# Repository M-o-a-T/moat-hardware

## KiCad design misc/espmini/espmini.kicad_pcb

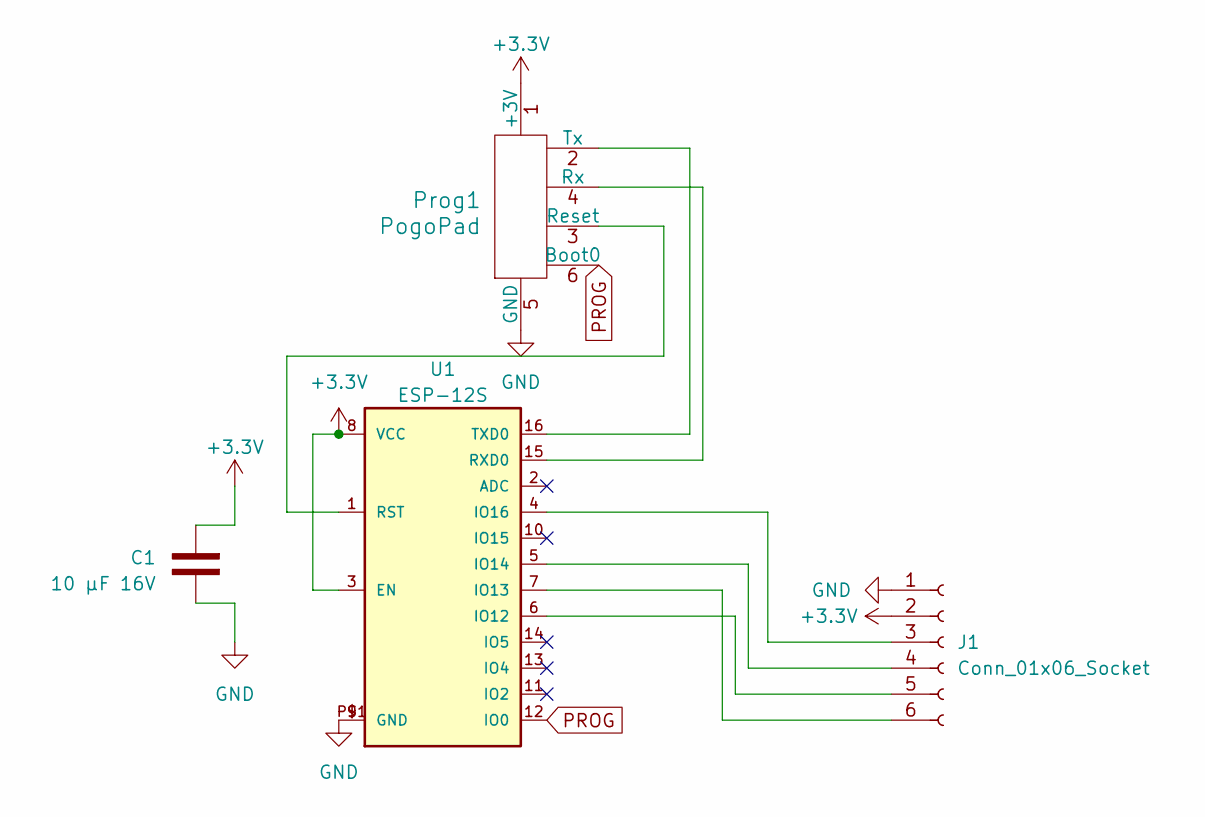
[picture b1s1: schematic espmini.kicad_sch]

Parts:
C1: CP_10µ_16V_0603; C_0805_2012Metric_Pad1.18x1.45mm_HandSolder
J1: Conn_01x06_Socket; Pads_1x06_P2.00mm
Prog1: PogoPad; 2X3_PAD
U1: ESP-12S

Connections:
+3V3: C1.1, J1.2, Prog1.1 (+3V), U1.3 (EN), U1.8 (VCC)
GND: C1.2, J1.1, Prog1.5 (GND), U1.9 (GND), U1.P$1 (GND)
unnamed: J1.3, U1.4 (IO16)
unnamed: J1.4, U1.5 (IO14)
unnamed: J1.5, U1.6 (IO12)
unnamed: J1.6, U1.7 (IO13)
unnamed: Prog1.3 (Reset), U1.1 (RST)
unnamed: Prog1.4 (Rx), U1.15 (RXD0)
unnamed: Prog1.2 (Tx), U1.16 (TXD0)
PROG: Prog1.6 (Boot0), U1.12 (IO0)

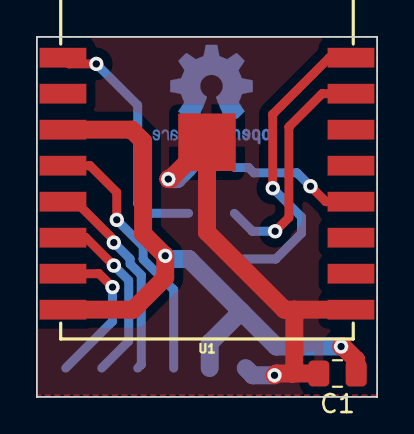
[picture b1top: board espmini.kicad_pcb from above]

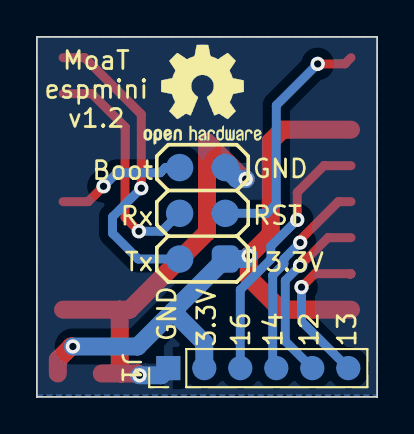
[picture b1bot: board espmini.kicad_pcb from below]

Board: 2 copper layers, 18.9 x 20.0 mm, 4 parts (2 on the bottom side), 10 nets.

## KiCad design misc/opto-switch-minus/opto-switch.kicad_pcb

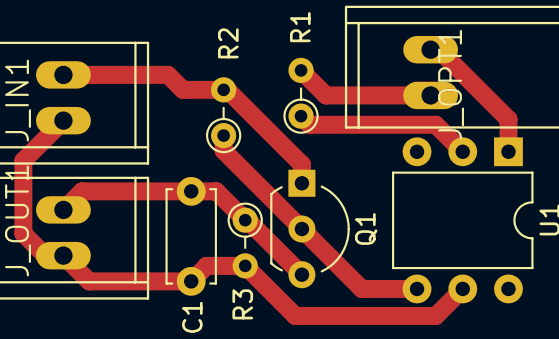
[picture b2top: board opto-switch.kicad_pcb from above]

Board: 2 copper layers, 9 parts (0 on the bottom side), 7 nets.

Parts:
C1: C; C_Disc_D5.0mm_W2.5mm_P5.00mm
J_IN1: Conn_01x02; 1X02_GN
J_OPT1: Conn_01x02; 1X02_GN
J_OUT1: Conn_01x02; 1X02_GN
Q1: 2N7002; TO-92L_Inline_Wide
R1: R_180_0603; R_Axial_DIN0204_L3.6mm_D1.6mm_P2.54mm_Vertical
R2: R 100k; R_Axial_DIN0204_L3.6mm_D1.6mm_P2.54mm_Vertical
R3: R 10k; R_Axial_DIN0204_L3.6mm_D1.6mm_P2.54mm_Vertical
U1: MOC8101; DIP-6_W7.62mm

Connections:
GND: J_IN1.2, Q1.1 (S), R2.2
unnamed: C1.1, J_IN1.1, J_OUT1.1, R3.2, U1.5
unnamed: J_OPT1.1, U1.1
unnamed: J_OPT1.2, R1.2
unnamed: C1.2, J_OUT1.2, Q1.3 (D), R3.1
unnamed: Q1.2 (G), R2.1, U1.4
unnamed: R1.1, U1.2

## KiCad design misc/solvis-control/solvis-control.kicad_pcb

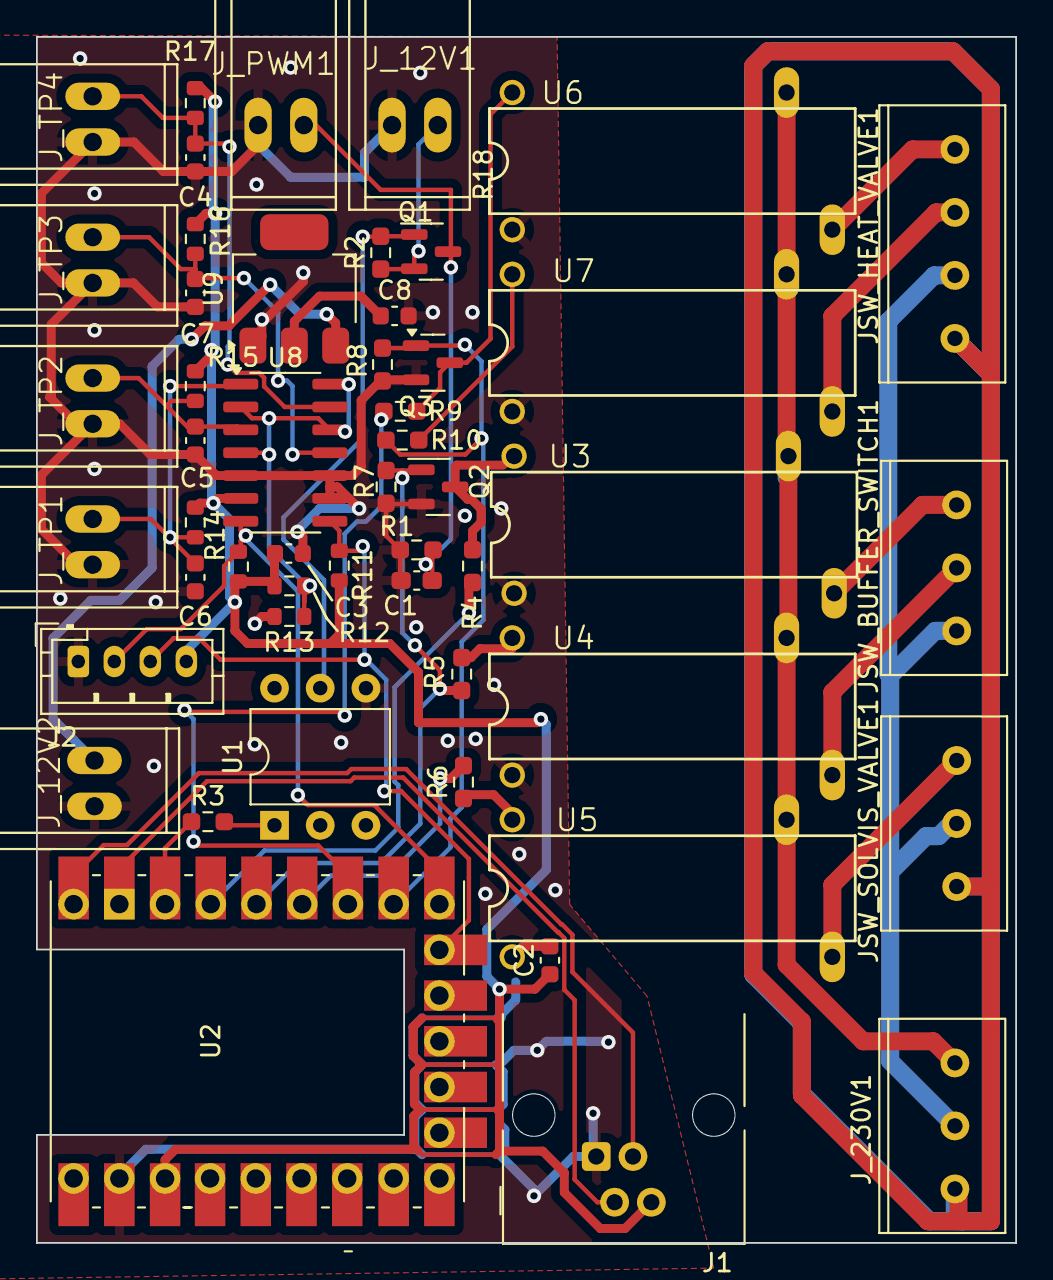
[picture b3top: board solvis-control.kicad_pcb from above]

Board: 2 copper layers, 54.4 x 67.0 mm, 51 parts (0 on the bottom side), 36 nets.

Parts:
C1: C; C_0603_1608Metric_Pad1.08x0.95mm_HandSolder
C2: CP_10µ_16V_0603; C_0603_1608Metric
C3: CP_1µ_0603; C_0603_1608Metric
C4, C5, C6, C7: CP_100n_50V_0603; C_0603_1608Metric
C8: C_1µ_25V_0603; C_0603_1608Metric
J1: Conn_01x04_Socket; RJ11
J2: Conn_01x04_Socket; JST_PH_B4B-PH-K_1x04_P2.00mm_Vertical
JSW_BUFFER_SWITCH1: Conn_01x03_Socket; Würth3.5mm_3
JSW_HEAT_VALVE1: Conn_01x04_Socket; Würth3.5mm_4
JSW_SOLVIS_VALVE1: Conn_01x03_Socket; Würth3.5mm_3
J_12V1, J_12V2: Conn_01x02; 1X02_GN
J_230V1: Conn_01x03_Socket; Würth3.5mm_3
J_PWM1: Conn_01x02; 1X02_GN
J_TP1, J_TP2, J_TP3, J_TP4: Conn_01x02; 1X02_GN
Q1: SI2390DS; SOT-23
Q2, Q3: 2N7002; SOT-23
R1: R 10k; R_0603_1608Metric_Pad0.98x0.95mm_HandSolder
R2, R7, R8: R 100k; R_0603_1608Metric_Pad0.98x0.95mm_HandSolder
R3: R_180_0603; R_0603_1608Metric_Pad0.98x0.95mm_HandSolder
R4, R5, R6, R9, R10: R_360_0603; R_0603_1608Metric_Pad0.98x0.95mm_HandSolder
R11, R12, R13, R14, R15, R16, R17, R18: R_1k_0603; R_0603_1608Metric
U1: MOC8101; DIP-6_W7.62mm
U2: RPi_Ali_SMD_TH
U3, U4, U5, U6, U7: CPC1965G; DIL16-CPC1965G
U8: MCP3428x-xSL; SOIC-14_3.9x8.7mm_P1.27mm
U9: AZ1117-3.3; SOT-223

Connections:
+3.3V: C2.1, C3.1, J1.4, J2.4, R11.2, R12.1, R14.2, R15.1, R16.2, R17.1, R18.2, U2.21 (3V3), U8.6 (V_{DD})
+3V3: C8.1, U9.2 (VO)
+12V: J_12V2.2, U9.3 (VI)
/ADCREF: R12.2, R13.1, U8.2 (CH1-), U8.4 (CH2-), U8.12 (CH3-), U8.14 (CH4-)
/L: J_230V1.1, U3.10 (A1), U4.10 (A1), U5.10 (A1), U6.10 (A1), U7.10 (A1)
/N: JSW_BUFFER_SWITCH1.3, JSW_HEAT_VALVE1.3, JSW_SOLVIS_VALVE1.2, J_230V1.2
/PE: JSW_HEAT_VALVE1.4, JSW_SOLVIS_VALVE1.3, J_230V1.3
/SCL: J2.3, R11.1, U2.10 (GPIO9), U8.8 (SCL)
/SDA: J2.2, R18.1, U2.9 (GPIO8), U8.7 (SDA)
GND: C1.2, C2.2, C3.2, C4.2, C5.2, C6.2, C7.2, C8.2, J1.1, J2.1, J_12V1.1, J_12V2.1, J_PWM1.1, J_TP1.1, J_TP2.1, J_TP3.1, J_TP4.1, Q2.2 (S), Q3.2 (S), R1.2, R7.2, R8.2, R13.2, U1.2, U1.4, U2.22 (GND), U3.1 (-), U4.1 (-), U5.1 (-), U6.1 (-), U7.1 (-), U8.5 (V_{SS}), U8.9 (Adr0), U8.10 (Adr1), U9.1 (ADJ)
unnamed: J1.2, U2.2 (GPIO1)
unnamed: J1.3, U2.1 (GPIO0)
unnamed: JSW_BUFFER_SWITCH1.1, U3.8 (A2)
unnamed: JSW_BUFFER_SWITCH1.2, U4.8 (A2)
unnamed: JSW_HEAT_VALVE1.1, U6.8 (A2)
unnamed: JSW_HEAT_VALVE1.2, U7.8 (A2)
unnamed: JSW_SOLVIS_VALVE1.1, U5.8 (A2)
unnamed: J_12V1.2, Q1.2 (S), R2.1
unnamed: C1.1, J_PWM1.2, Q1.3 (D), R1.1
unnamed: C6.1, J_TP1.2, R14.1, U8.1 (CH1+)
unnamed: C5.1, J_TP2.2, R15.2, U8.3 (CH2+)
unnamed: C7.1, J_TP3.2, R16.1, U8.11 (CH3+)
unnamed: C4.1, J_TP4.2, R17.2, U8.13 (CH4+)
unnamed: Q1.1 (G), R2.2, U1.5
unnamed: Q2.3 (D), R4.1, U3.16 (+)
unnamed: Q2.1 (G), R5.2, R7.1, U2.5 (GPIO4)
unnamed: Q3.3 (D), R9.1, U6.16 (+)
unnamed: Q3.1 (G), R8.1, R10.2, U2.8 (GPIO7)
unnamed: R3.2, U1.1
unnamed: R3.1, U2.3 (GPIO2)
unnamed: R4.2, U2.4 (GPIO3)
unnamed: R6.2, U2.6 (GPIO5)
unnamed: R9.2, U2.7 (GPIO6)
unnamed: R5.1, U4.16 (+)
unnamed: R6.1, U5.16 (+)
unnamed: R10.1, U7.16 (+)

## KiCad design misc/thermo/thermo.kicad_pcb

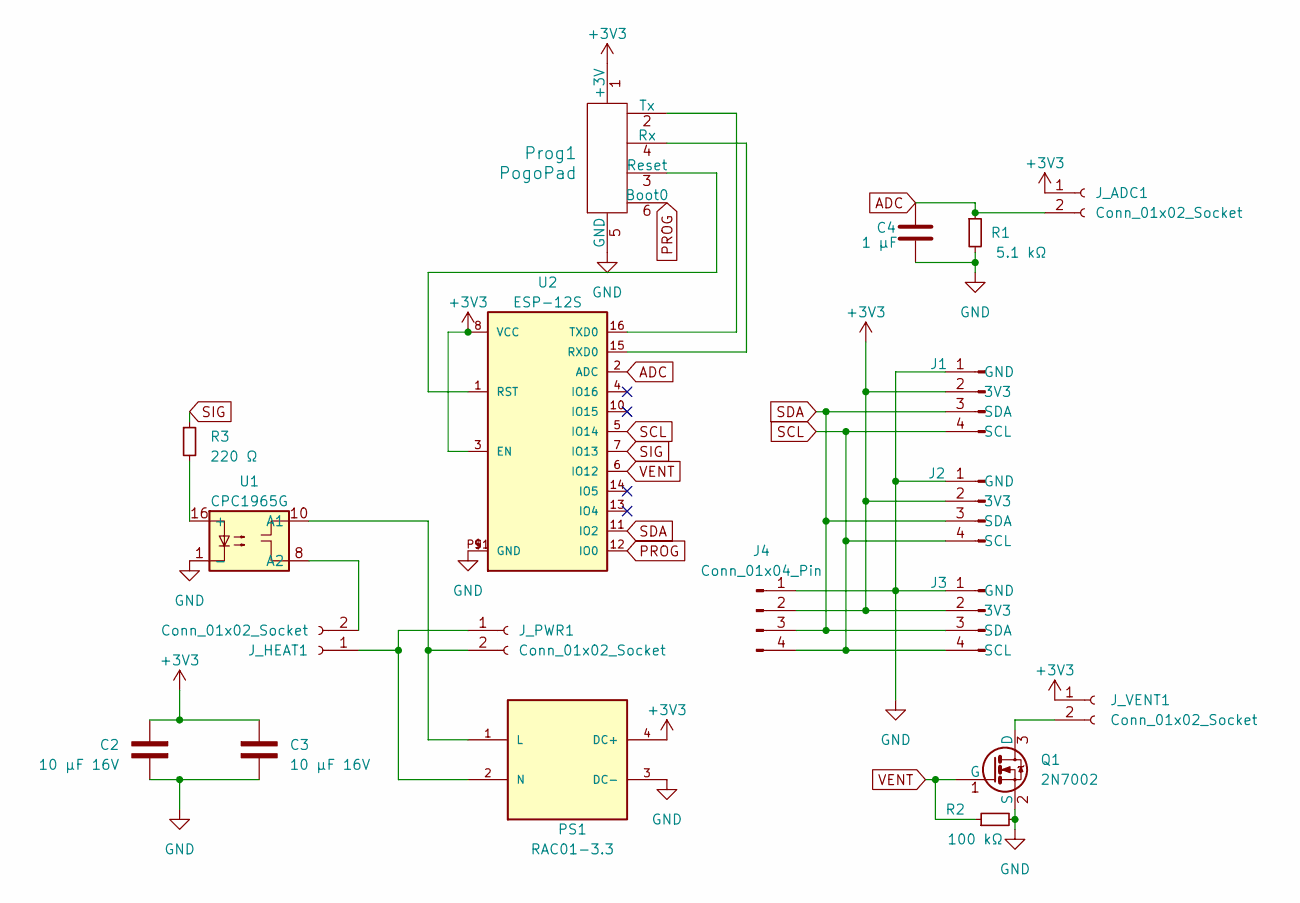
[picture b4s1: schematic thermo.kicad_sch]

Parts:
C2, C3: CP_10µ_16V_0603; C_0603_1608Metric
C4: CP_1µ_10V_0603; C_0603_1608Metric; Farnell 3013419
J1, J2, J3: Conn_01x04_Pin; JST_SH_BM04B-SRSS-TB_1x04-1MP_P1.00mm_Vertical
J4: Conn_01x04_Pin; PinHeader_1x04_P2.54mm_Vertical
J_ADC1: Conn_01x02_Socket; JST_XA_B02B-XASK-1_1x02_P2.50mm_Vertical
J_HEAT1: Conn_01x02_Socket; 1X02_GN
J_PWR1: Conn_01x02_Socket; 1X02_GN
J_VENT1: Conn_01x02_Socket; JST_XA_B02B-XASK-1_1x02_P2.50mm_Vertical
PS1: RAC01-3.3
Prog1: PogoPad; 2X3_PAD
Q1: 2N7002; SOT-23
R1: R_5k1_0603; R_0603_1608Metric; LCSC C23186
R2: R_100k_0603; R_0603_1608Metric
R3: R_220_0603; R_0603_1608Metric
U1: CPC1965G; DIL16-CPC1965G
U2: ESP-12S

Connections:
+3V3: C2.1, C3.1, J1.2 (3V3), J2.2 (3V3), J3.2 (3V3), J4.2, J_ADC1.1, J_VENT1.1, PS1.4 (DC+), Prog1.1 (+3V), U2.3 (EN), U2.8 (VCC)
ADC: C4.1, J_ADC1.2, R1.1, U2.2 (ADC)
GND: C2.2, C3.2, C4.2, J1.1 (GND), J2.1 (GND), J3.1 (GND), J4.1, PS1.3 (DC-), Prog1.5 (GND), Q1.2 (S), R1.2, R2.2, U1.1 (-), U2.9 (GND), U2.P$1 (GND)
unnamed: J_HEAT1.1, J_PWR1.1, PS1.2 (N)
unnamed: J_HEAT1.2, U1.8 (A2)
unnamed: J_PWR1.2, PS1.1 (L), U1.10 (A1)
unnamed: J_VENT1.2, Q1.3 (D)
unnamed: Prog1.3 (Reset), U2.1 (RST)
unnamed: Prog1.4 (Rx), U2.15 (RXD0)
unnamed: Prog1.2 (Tx), U2.16 (TXD0)
unnamed: R3.2, U1.16 (+)
PROG: Prog1.6 (Boot0), U2.12 (IO0)
SCL: J1.4 (SCL), J2.4 (SCL), J3.4 (SCL), J4.4, U2.5 (IO14)
SDA: J1.3 (SDA), J2.3 (SDA), J3.3 (SDA), J4.3, U2.11 (IO2)
SIG: R3.1, U2.7 (IO13)
VENT: Q1.1 (G), R2.1, U2.6 (IO12)

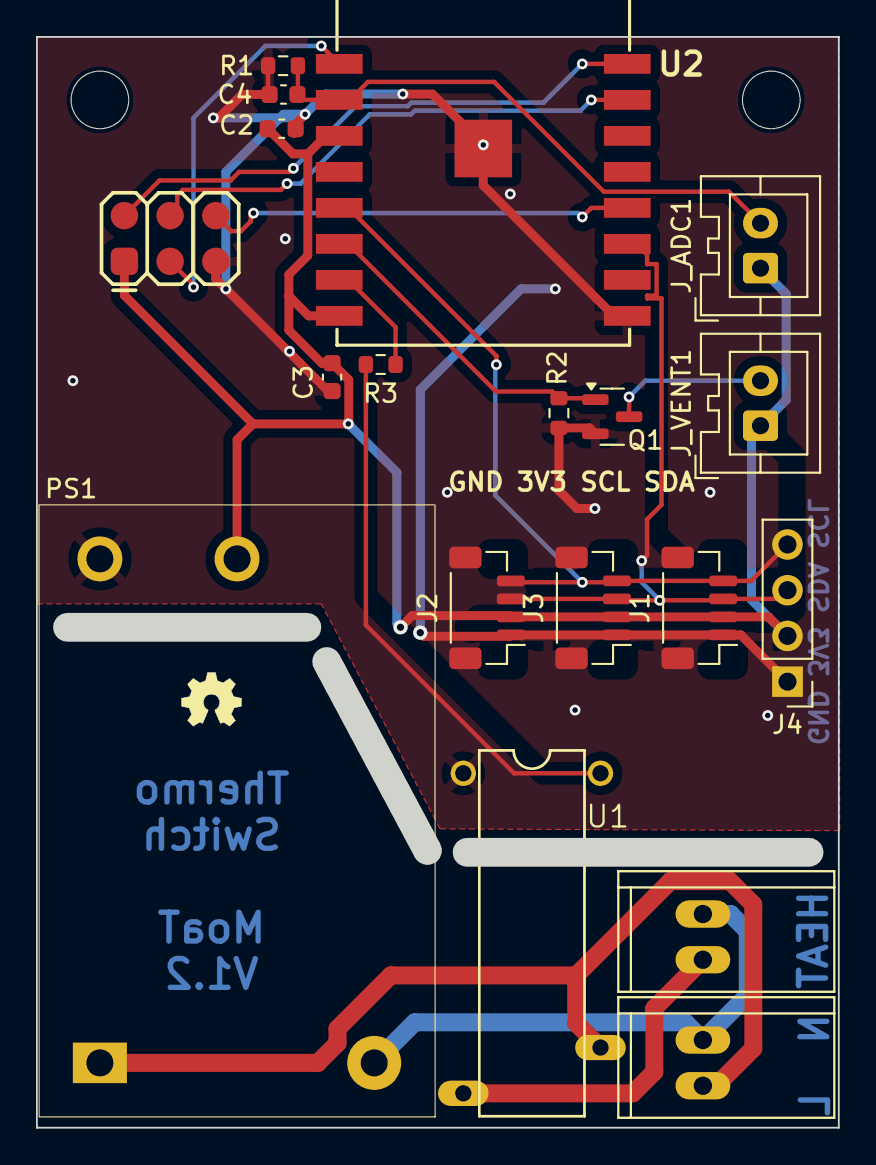
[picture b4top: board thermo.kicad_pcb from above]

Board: 2 copper layers, 44.5 x 60.6 mm, 19 parts (0 on the bottom side), 16 nets.

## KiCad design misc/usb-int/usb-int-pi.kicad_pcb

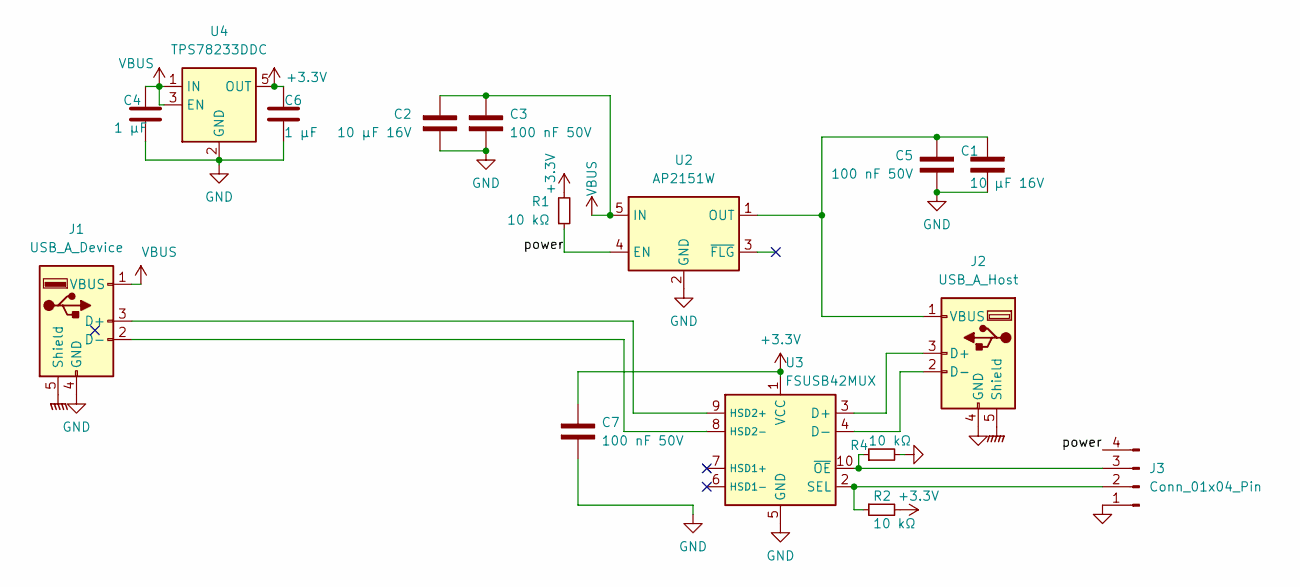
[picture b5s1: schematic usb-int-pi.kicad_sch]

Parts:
C1, C2: CP_10µ_16V_0603; C_0603_1608Metric
C3, C5, C7: CP_100n_16V_0603; C_0603_1608Metric; Farnell 3881081
C4, C6: CP_1µ_10V_0603; C_0603_1608Metric; Farnell 3013419
J1: USB_A_Device; SAMTEC_USB-AM-S-X-X-TH; Farnell 3551287
J2: USB_A_Host; USB_A_Stewart_SS-52100-001_Horizontal; Farnell 4126367
J3: Conn_01x04_Pin; PinHeader_1x04_P2.54mm_Horizontal
R1, R2, R4: R_10k_0603; R_0603_1608Metric; LCSC C25804
U2: AP2151W; SOT-23-5; Farnell 3482805
U3: FSUSB42MUX; MSOP-10_3x3mm_P0.5mm; Farnell 2564479
U4: TPS78233DDC; SOT-23-5

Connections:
+3V3: C6.1, C7.1, R1.2, R2.2, U3.1 (VCC), U4.5 (OUT)
/power: J3.4, R1.1, U2.4 (EN)
GND: C1.2, C2.2, C3.2, C4.2, C5.2, C6.2, C7.2, J1.4 (GND), J2.4 (GND), J3.1, R4.2, U2.2 (GND), U3.5 (GND), U4.2 (GND), U4.4 (GND)
GNDPWR: J1.5 (Shield), J2.5 (Shield)
unnamed: J1.3 (D+), U3.9 (HSD2+)
unnamed: J1.2 (D-), U3.8 (HSD2-)
unnamed: J2.3 (D+), U3.3 (D+)
unnamed: J2.2 (D-), U3.4 (D-)
unnamed: C1.1, C5.1, J2.1 (VBUS), U2.1 (OUT)
unnamed: J3.2, R2.1, U3.2 (SEL)
unnamed: J3.3, R4.1, U3.10 (~OE)
VBUS: C2.1, C3.1, C4.1, J1.1 (VBUS), U2.5 (IN), U4.1 (IN), U4.3 (EN)

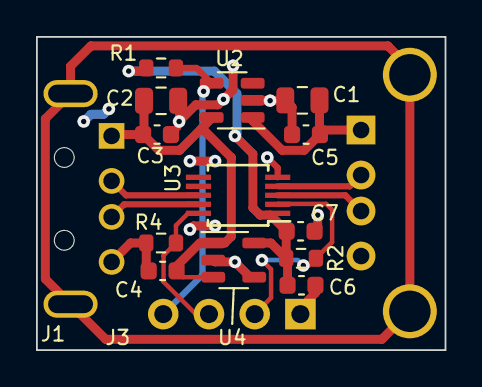
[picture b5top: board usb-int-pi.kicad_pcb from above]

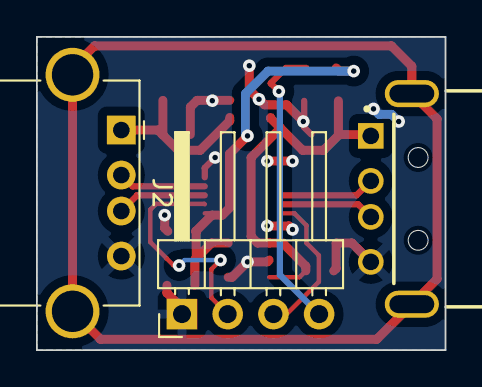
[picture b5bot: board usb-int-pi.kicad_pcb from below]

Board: 2 copper layers, 22.7 x 17.4 mm, 16 parts (3 on the bottom side), 12 nets.

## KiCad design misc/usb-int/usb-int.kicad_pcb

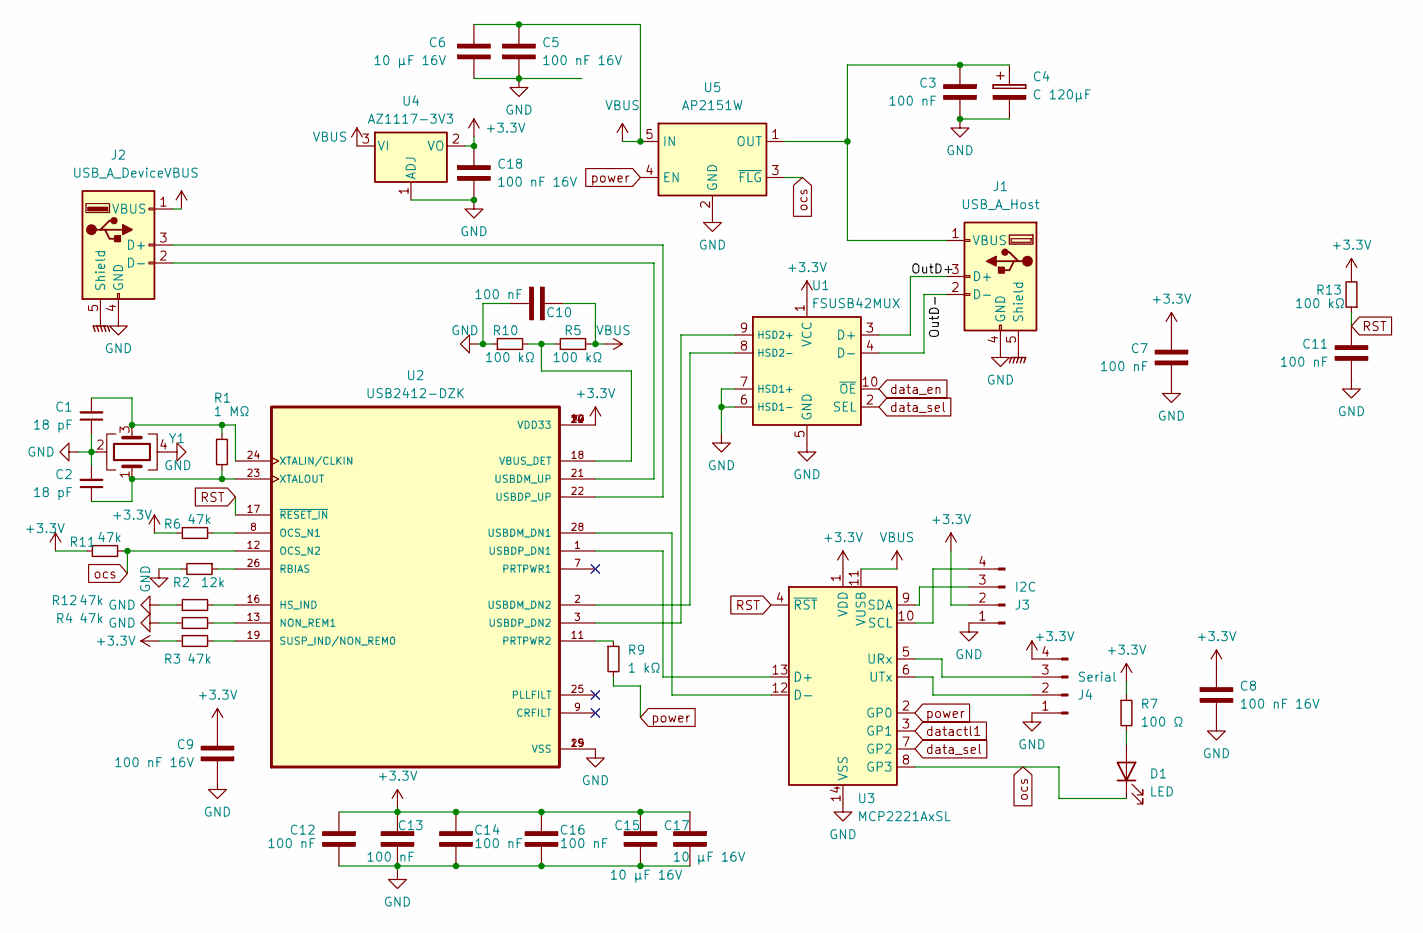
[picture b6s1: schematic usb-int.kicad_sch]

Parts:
C1, C2: 18 pF; C_0603_1608Metric; Farnell 1759056
C3, C5, C7, C8, C9, C10, C11, C12, C13, C14, C16, C18: CP_100n_16V_0603; C_0603_1608Metric; Farnell 3881081
C4: C 120µF; C_Elec_5x5.4; Farnell 2466648
C6, C15, C17: CP_10µ_16V_0603; C_0603_1608Metric
D1: LED; LED_0603_1608Metric
J1: USB_A_Host; USB_A_Stewart_SS-52100-001_Horizontal
J2: USB_A_Device; SAMTEC_USB-AM-S-X-X-TH; Farnell 3551287
J3: I2C; JST_SH_SM04B-SRSS-TB_1x04-1MP_P1.00mm_Horizontal; Farnell 1830839
J4: Serial; JST_SH_SM04B-SRSS-TB_1x04-1MP_P1.00mm_Horizontal; Farnell 2399347
R1: R_1M_0603; R_0603_1608Metric; LCSC C22935
R2: 12k; R_0603_1608Metric; Farnell 2670002
R3, R4, R6, R11, R12: 47k; R_0603_1608Metric; Farnell 4004545
R5, R10, R13: R_100k_0603; R_0603_1608Metric
R7: R_100_0603; R_0603_1608Metric; LCSC C22775
R9: R_1k_0603; R_0603_1608Metric; LCSC C21190
U1: FSUSB42MUX; MSOP-10_3x3mm_P0.5mm; Farnell 1495467
U2: USB2412-DZK; QFN-28-1EP_5x5mm_P0.5mm_EP3.35x3.35mm; DIGI-KEY_PART_NUMBER 638-1114-ND
U3: MCP2221AxSL; SOIC-14_3.9x8.7mm_P1.27mm
U4: AZ1117-3V3; SOT-223; LCSC C108492
U5: AP2151W; SOT-23-5; Farnell 1843872
Y1: Crystal_GND24; Crystal_SMD_2522-4Pin_2.5x2.2mm; Farnell 3573028

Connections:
+3V3: C7.1, C8.1, C9.1, C12.1, C13.1, C14.1, C15.1, C16.1, C17.1, C18.1, J3.2, J4.4, R3.1, R6.1, R7.1, R11.1, R13.2, U1.1 (VCC), U2.4 (VDD33), U2.10 (VDD33), U2.14 (VDD33), U2.20 (VDD33), U2.27 (VDD33), U3.1 (VDD), U4.2 (VO)
/OutD+: J1.3 (D+), U1.3 (D+)
/OutD-: J1.2 (D-), U1.4 (D-)
GND: C1.1, C2.2, C3.2, C4.2, C5.2, C6.2, C7.2, C8.2, C9.2, C10.1, C11.2, C12.2, C13.2, C14.2, C15.2, C16.2, C17.2, C18.2, J1.4 (GND), J2.4 (GND), J3.1, J4.1, R2.2, R4.1, R10.1, R12.1, U1.5 (GND), U1.6 (HSD1-), U1.7 (HSD1+), U2.15 (VSS), U2.29 (VSS), U3.14 (VSS), U4.1 (ADJ), U5.2 (GND), Y1.2, Y1.4
GNDPWR: J1.5 (Shield), J2.5 (Shield)
unnamed: D1.2 (A), R7.2
unnamed: C3.1, C4.1, J1.1 (VBUS), U5.1 (OUT)
unnamed: J2.3 (D+), U2.22 (USBDP_UP)
unnamed: J2.2 (D-), U2.21 (USBDM_UP)
unnamed: J3.3, U3.9 (SDA)
unnamed: J3.4, U3.10 (SCL)
unnamed: J4.2, U3.6 (UTx)
unnamed: J4.3, U3.5 (URx)
unnamed: U1.9 (HSD2+), U2.3 (USBDP_DN2)
unnamed: U1.8 (HSD2-), U2.2 (USBDM_DN2)
unnamed: R12.2, U2.16 (HS_IND)
unnamed: R4.2, U2.13 (NON_REM1)
unnamed: R6.2, U2.8 (OCS_N1)
unnamed: R9.1, U2.11 (PRTPWR2)
unnamed: R2.1, U2.26 (RBIAS)
unnamed: R3.2, U2.19 (SUSP_IND/NON_REM0)
unnamed: U2.28 (USBDM_DN1), U3.12 (D-)
unnamed: U2.1 (USBDP_DN1), U3.13 (D+)
unnamed: R5.1, R10.2, U2.18 (VBUS_DET)
unnamed: C1.2, R1.1, U2.24 (XTALIN/CLKIN), Y1.3
unnamed: C2.1, R1.2, U2.23 (XTALOUT), Y1.1
RST: C11.1, R13.1, U2.17 (~RESET_IN), U3.4 (~RST)
VBUS: C5.1, C6.1, C10.2, J2.1 (VBUS), R5.2, U3.11 (VUSB), U4.3 (VI), U5.5 (IN)
data_en: U1.10 (~OE)
data_sel: U1.2 (SEL), U3.7 (GP2)
datactl1: U3.3 (GP1)
ocs: D1.1 (K), R11.2, U2.12 (OCS_N2), U3.8 (GP3), U5.3 (~FLG)
power: R9.2, U3.2 (GP0), U5.4 (EN)

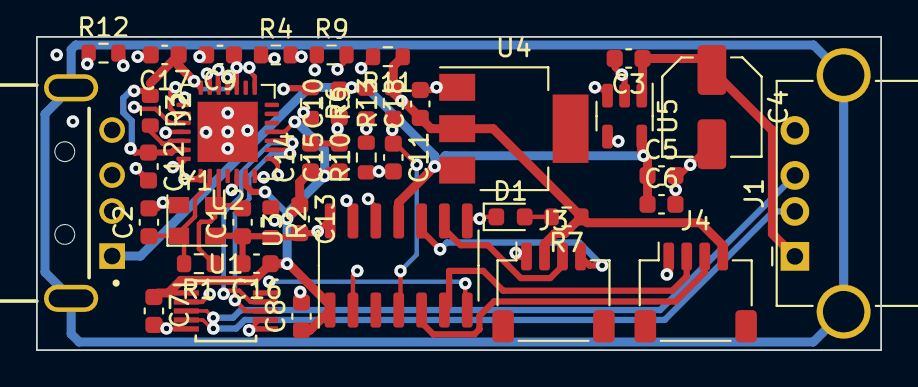
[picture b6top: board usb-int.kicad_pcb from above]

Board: 4 copper layers, 46.9 x 17.4 mm, 41 parts (0 on the bottom side), 31 nets.

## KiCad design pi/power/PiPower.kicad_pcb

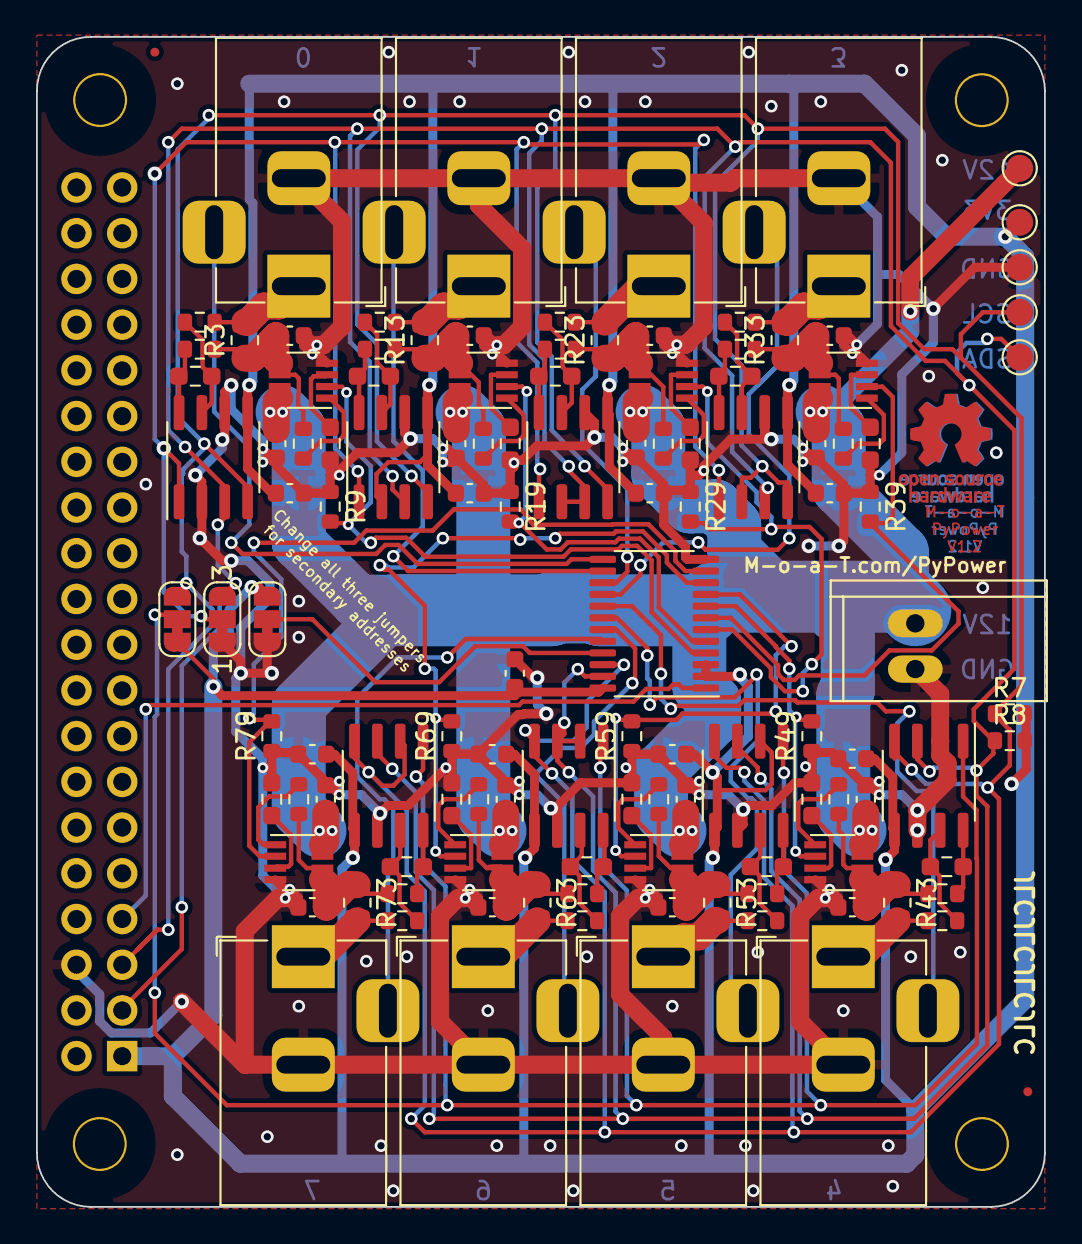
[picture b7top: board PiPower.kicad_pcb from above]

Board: 2 copper layers, 56.0 x 65.0 mm, 122 parts (1 on the bottom side), 73 nets.

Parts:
C1, C3, C6, C7, C9, C12, C13, C15, C17, C23, C26, C27, C30, C32, C33, C36: 10µF; C_0603_1608Metric
C2, C8, C10, C11, C18, C28, C29, C31: 0; R_0603_1608Metric_Pad0.98x0.95mm_HandSolder
C4, C14, C16, C19, C24, C34, C35, C37, C41: .1µF; C_0603_1608Metric
C5, C20, C21, C22, C25, C38, C39, C40: 1µ; R_0603_1608Metric_Pad0.98x0.95mm_HandSolder
H1, H2, H3, H4: 3mm_Mounting_Hole; NPTH_3mm_ID
J1: Raspberry_Pi_2_3; PinSocket_2x20_P2.54mm_Vertical
J2: Power; 1X02_GN
J3: Out 0; Barrel Jack locking
J4: Out 1; Barrel Jack locking
J5: Out 2; Barrel Jack locking
J6: Out 3; Barrel Jack locking
J7: Out 4; Barrel Jack locking
J8: Out 5; Barrel Jack locking
J9: Out 7; Barrel Jack locking
J10: Out 6; Barrel Jack locking
JP1, JP2, JP3: Jumper_3_Bridged12; SolderJumper-3_P1.3mm_Bridged12_RoundedPad1.0x1.5mm_NumberL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
R1, R11, R21, R31, R41, R51, R61, R71: 22; R_0603_1608Metric
R2, R4, R12, R14, R22, R24, R32, R34, R42, R44, R52, R54, R62, R64, R72, R74: 10; R_0603_1608Metric
R3, R13, R23, R33, R43, R53, R63, R73: .1; R_0805_2012Metric
R7, R8: 1k; R_0603_1608Metric
R9, R19, R29, R39, R49, R59, R69, R79: 10k; R_0603_1608Metric
TP1, TP2, TP3, TP4, TP5: TestPoint; TestPoint_Pad_D1.5mm
U1, U3, U4, U5, U8, U11, U12, U13: MP5014A; TSOT-23-8
U2, U6, U7, U9, U10, U14, U15, U16: INA219AxD; SOIC-8_3.9x4.9mm_P1.27mm
U17: PCAL6416APW; TSSOP-24_4.4x7.8mm_P0.65mm

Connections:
+3V3: C4.1, C14.1, C16.1, C19.1, C24.1, C34.1, C35.1, C37.1, C41.1, J1.1 (3V3), JP2.1 (A), JP3.3 (B), R7.2, R8.2, TP2.1, U2.5 (VS), U6.2 (A0), U6.5 (VS), U7.5 (VS), U9.5 (VS), U10.5 (VS), U14.2 (A0), U14.5 (VS), U15.5 (VS), U16.5 (VS), U17.2 (VDD_I2C), U17.3 (~RESET), U17.24 (VDD_P)
+12V: C1.1, C6.1, C7.1, C9.1, C13.1, C26.1, C27.1, C30.1, J2.1, TP3.1, U1.7 (Vcc), U1.8 (Vcc), U3.7 (Vcc), U3.8 (Vcc), U4.7 (Vcc), U4.8 (Vcc), U5.7 (Vcc), U5.8 (Vcc), U8.7 (Vcc), U8.8 (Vcc), U11.7 (Vcc), U11.8 (Vcc), U12.7 (Vcc), U12.8 (Vcc), U13.7 (Vcc), U13.8 (Vcc)
/The other seven/V12O1: J4.1, R13.2, R14.2
/The other seven/V12O2: J5.1, R23.2, R24.2
/The other seven/V12O3: J6.1, R33.2, R34.2
/The other seven/V12O4: J7.1, R43.2, R44.2
/The other seven/V12O5: J8.1, R53.2, R54.2
/The other seven/V12O6: J10.1, R63.2, R64.2
/The other seven/V12O7: J9.1, R73.2, R74.2
/The other seven/V12P1: C12.1, R11.2, R12.2, R13.1, U3.5 (Source), U3.6 (Source)
/The other seven/V12P2: C15.1, R21.2, R22.2, R23.1, U4.5 (Source), U4.6 (Source)
/The other seven/V12P3: C17.1, R31.2, R32.2, R33.1, U5.5 (Source), U5.6 (Source)
/The other seven/V12P4: C23.1, R41.2, R42.2, R43.1, U8.5 (Source), U8.6 (Source)
/The other seven/V12P5: C32.1, R51.2, R52.2, R53.1, U11.5 (Source), U11.6 (Source)
/The other seven/V12P6: C36.1, R61.2, R62.2, R63.1, U13.5 (Source), U13.6 (Source)
/V12O0: J3.1, R3.2, R4.2
/V12P0: C3.1, R1.2, R2.2, R3.1, U1.5 (Source), U1.6 (Source)
ENA0: R9.2, U1.2 (Enable/Fault), U17.4 (P0_0)
ENA1: R19.2, U3.2 (Enable/Fault), U17.5 (P0_1)
ENA2: R29.2, U4.2 (Enable/Fault), U17.6 (P0_2)
ENA3: R39.2, U5.2 (Enable/Fault), U17.7 (P0_3)
ENA4: R49.2, U8.2 (Enable/Fault), U17.8 (P0_4)
ENA5: R59.2, U11.2 (Enable/Fault), U17.9 (P0_5)
ENA6: R69.2, U13.2 (Enable/Fault), U17.10 (P0_6)
ENA7: R79.2, U12.2 (Enable/Fault), U17.11 (P0_7)
GND: C1.2, C2.2, C3.2, C4.2, C6.2, C7.2, C8.2, C9.2, C10.2, C11.2, C12.2, C13.2, C14.2, C15.2, C16.2, C17.2, C18.2, C19.2, C23.2, C24.2, C26.2, C27.2, C28.2, C29.2, C30.2, C31.2, C32.2, C33.2, C34.2, C35.2, C36.2, C37.2, C41.2, J1.6 (GND), J2.2, J3.2, J4.2, J5.2, J6.2, J7.2, J8.2, J9.2, J10.2, JP1.1 (A), JP3.1 (A), R9.1, R19.1, R29.1, R39.1, R49.1, R59.1, R69.1, R79.1, TP1.1, U1.4 (GND), U2.2 (A0), U2.6 (GND), U3.4 (GND), U4.4 (GND), U5.4 (GND), U6.6 (GND), U7.6 (GND), U8.4 (GND), U9.6 (GND), U10.2 (A0), U10.6 (GND), U11.4 (GND), U12.4 (GND), U13.4 (GND), U14.6 (GND), U15.6 (GND), U16.6 (GND), U17.12 (VSS)
unnamed: J1.7 (GCLK0/GPIO4), U17.1 (~INT)
unnamed: C2.1, U1.3 (DV/DT)
unnamed: R1.1, U1.1 (I-Limit)
unnamed: C5.1, R2.1, U2.8 (IN+)
unnamed: C5.2, R4.1, U2.7 (IN-)
unnamed: C8.1, U3.3 (DV/DT)
unnamed: R11.1, U3.1 (I-Limit)
unnamed: C10.1, U4.3 (DV/DT)
unnamed: R21.1, U4.1 (I-Limit)
unnamed: C11.1, U5.3 (DV/DT)
unnamed: R31.1, U5.1 (I-Limit)
unnamed: C20.1, R12.1, U6.8 (IN+)
unnamed: C20.2, R14.1, U6.7 (IN-)
unnamed: C21.1, R22.1, U7.8 (IN+)
unnamed: C21.2, R24.1, U7.7 (IN-)
unnamed: C18.1, U8.3 (DV/DT)
unnamed: R41.1, U8.1 (I-Limit)
unnamed: C22.1, R32.1, U9.8 (IN+)
unnamed: C22.2, R34.1, U9.7 (IN-)
unnamed: C25.1, R42.1, U10.8 (IN+)
unnamed: C25.2, R44.1, U10.7 (IN-)
unnamed: C28.1, U11.3 (DV/DT)
unnamed: R51.1, U11.1 (I-Limit)
unnamed: C29.1, U12.3 (DV/DT)
unnamed: R71.1, U12.1 (I-Limit)
unnamed: C33.1, R71.2, R72.2, R73.1, U12.5 (Source), U12.6 (Source)
unnamed: C31.1, U13.3 (DV/DT)
unnamed: R61.1, U13.1 (I-Limit)
unnamed: C38.1, R52.1, U14.8 (IN+)
unnamed: C38.2, R54.1, U14.7 (IN-)
unnamed: C39.1, R72.1, U15.8 (IN+)
unnamed: C39.2, R74.1, U15.7 (IN-)
unnamed: C40.1, R62.1, U16.8 (IN+)
unnamed: C40.2, R64.1, U16.7 (IN-)
SCL: J1.5 (SCL/GPIO3), JP2.3 (B), R7.1, TP4.1, U2.4 (SCL), U6.4 (SCL), U7.4 (SCL), U9.2 (A0), U9.4 (SCL), U10.4 (SCL), U14.4 (SCL), U15.2 (A0), U15.4 (SCL), U16.4 (SCL), U17.22 (SCL)
SDA: J1.3 (SDA/GPIO2), JP1.3 (B), R8.1, TP5.1, U2.3 (SDA), U6.3 (SDA), U7.2 (A0), U7.3 (SDA), U9.3 (SDA), U10.3 (SDA), U14.3 (SDA), U15.3 (SDA), U16.2 (A0), U16.3 (SDA), U17.23 (SDA)
SEL: JP3.2 (C), U17.21 (ADDR)
SEL03: JP1.2 (C), U2.1 (A1), U6.1 (A1), U7.1 (A1), U9.1 (A1)
SEL47: JP2.2 (C), U10.1 (A1), U14.1 (A1), U15.1 (A1), U16.1 (A1)
SENS0: J3.3, U17.13 (P1_0)
SENS1: J4.3, U17.14 (P1_1)
SENS2: J5.3, U17.15 (P1_2)
SENS3: J6.3, U17.16 (P1_3)
SENS4: J7.3, U17.17 (P1_4)
SENS5: J8.3, U17.18 (P1_5)
SENS6: J10.3, U17.19 (P1_6)
SENS7: J9.3, U17.20 (P1_7)
